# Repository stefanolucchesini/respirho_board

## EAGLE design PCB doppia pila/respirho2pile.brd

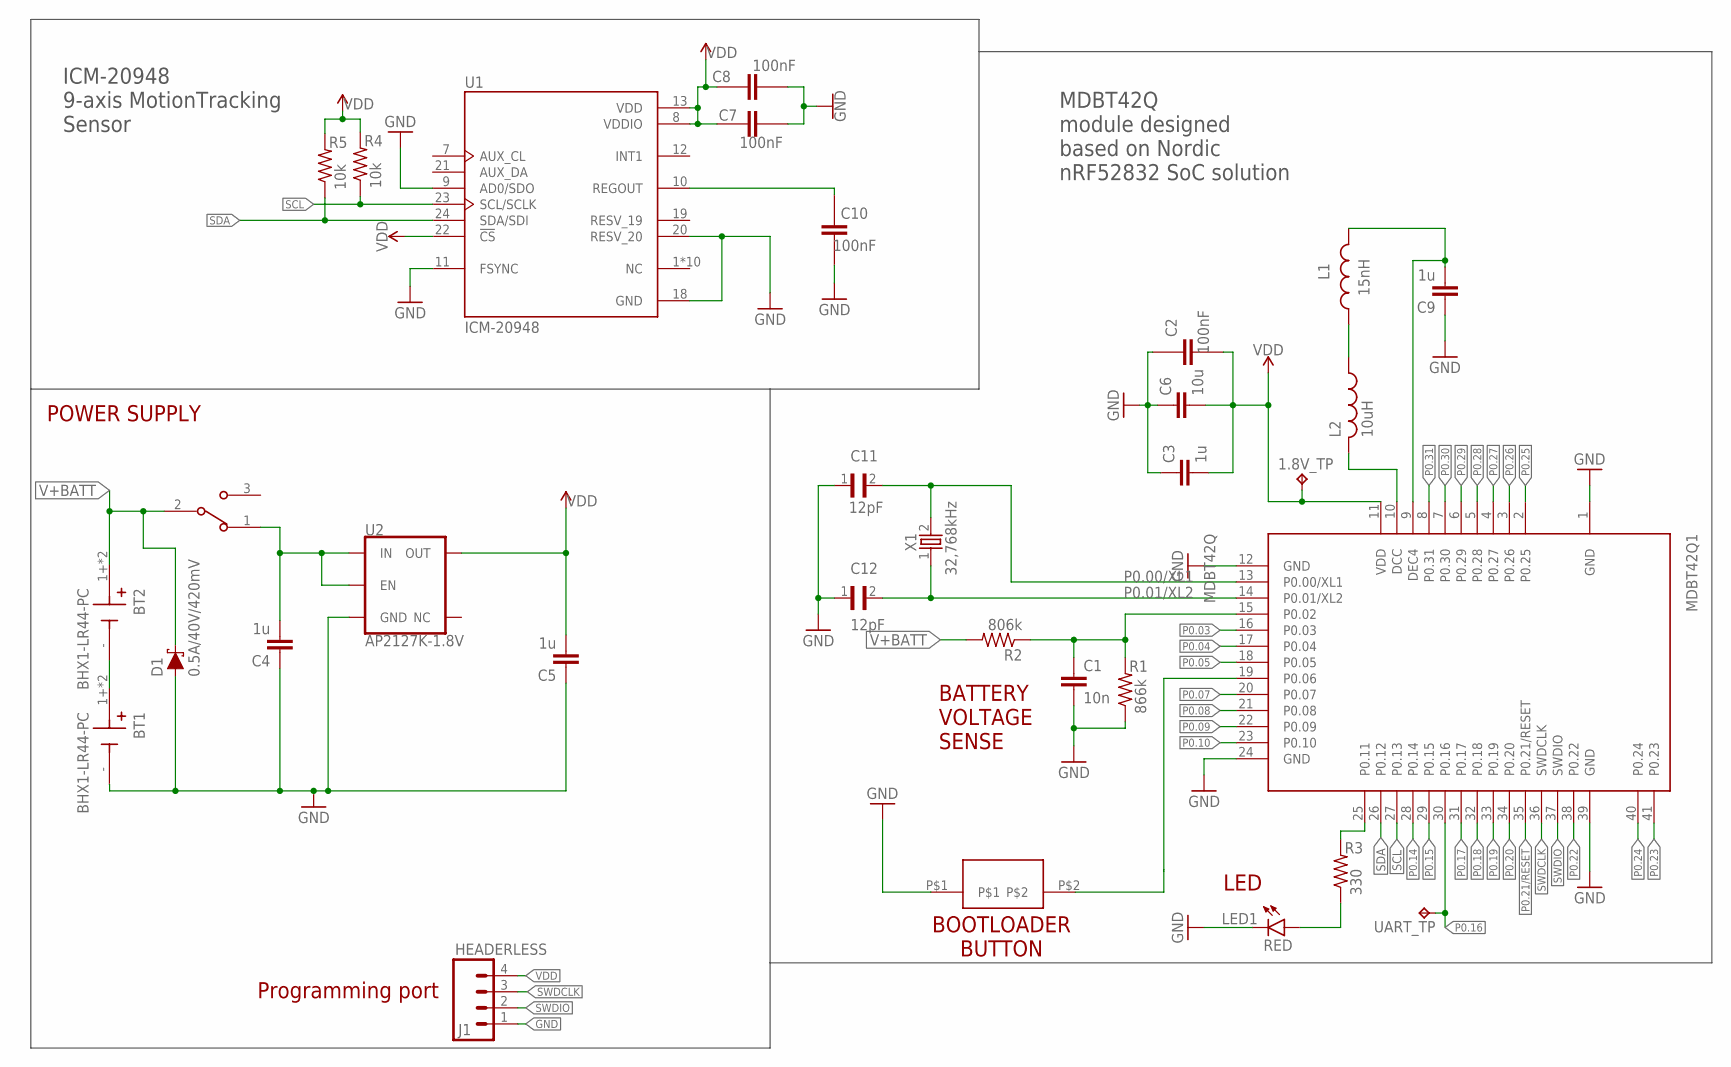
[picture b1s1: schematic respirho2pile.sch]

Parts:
1.8V_TP: TPB1,27; B1,27
BT1, BT2: BHX1-LR44-PC; BAT_BHX1-LR44-PC
C1: 10n; C0603
C2, C7, C8, C10: 100nF; CAPC1005X60
C3, C4, C5, C9: 1u; C0603
C6: 10u; C2012
C11, C12: 12pF; CAPC1005X56N
D1: 0.5A/40V/420mV; SOD-323
J1: HEADERLESS; 1X04
L1: 15nH; INDC1005X55N
L2: 10uH; RESC0603_L
LED1: RED; CHIPLED_1206
MDBT42Q1: MDBT42Q
R1: 866k; R0402
R2: 806k; R0402
R3: 330; R0402
R4, R5: 10k; R0402
SW1: EG1213; SW_EG1213
SW2: KSS231GLFS
U1: ICM-20948; QFN40P300X300X105-24N
U2: AP2127K-1.8V; SOT23-5
UART_TP: TPB1,27; B1,27
X1: 32,768kHz; XTAL_3215_N

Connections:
GND: BT1.-, C1.2, C2.2, C3.1, C4.1, C5.1, C6.1, C7.1, C8.1, C9.1, C10.1, C11.1, C12.1, D1.A, J1.1, LED1.C, MDBT42Q1.1 (GND), MDBT42Q1.12 (GND), MDBT42Q1.24 (GND), MDBT42Q1.39 (GND), R1.1, SW2.P$1, U1.9 (AD0/SDO), U1.11 (FSYNC), U1.18 (GND), U1.20 (RESV_20), U2.2 (GND)
unnamed: LED1.A, R3.1
unnamed: L2.2, MDBT42Q1.10 (DCC)
unnamed: L1.1, L2.1
unnamed: C9.2, L1.2, MDBT42Q1.9 (DEC4)
unnamed: MDBT42Q1.25 (P0.11), R3.2
unnamed: BT1.1+ (+), BT1.2+ (+), BT2.-
unnamed: C10.2, U1.10 (REGOUT)
unnamed: C4.2, SW1.1, U2.1 (IN), U2.3 (EN)
unnamed: C1.1, MDBT42Q1.15 (P0.02), R1.2, R2.1
P0.00/XL1: C11.2, MDBT42Q1.13 (P0.00/XL1), X1.2
P0.01/XL2: C12.2, MDBT42Q1.14 (P0.01/XL2), X1.1
P0.03: MDBT42Q1.16 (P0.03)
P0.04: MDBT42Q1.17 (P0.04)
P0.05: MDBT42Q1.18 (P0.05)
P0.07: MDBT42Q1.20 (P0.07)
P0.08: MDBT42Q1.21 (P0.08)
P0.09: MDBT42Q1.22 (P0.09)
P0.10: MDBT42Q1.23 (P0.10)
P0.14: MDBT42Q1.28 (P0.14)
P0.15: MDBT42Q1.29 (P0.15)
P0.16: MDBT42Q1.30 (P0.16), UART_TP.TP
P0.17: MDBT42Q1.31 (P0.17)
P0.18: MDBT42Q1.32 (P0.18)
P0.19: MDBT42Q1.33 (P0.19)
P0.20: MDBT42Q1.34 (P0.20)
P0.21/RESET: MDBT42Q1.35 (P0.21/RESET)
P0.22: MDBT42Q1.38 (P0.22)
P0.23: MDBT42Q1.41 (P0.23)
P0.24: MDBT42Q1.40 (P0.24)
P0.25: MDBT42Q1.2 (P0.25)
P0.26: MDBT42Q1.3 (P0.26)
P0.27: MDBT42Q1.4 (P0.27)
P0.28: MDBT42Q1.5 (P0.28)
P0.29: MDBT42Q1.6 (P0.29)
P0.30: MDBT42Q1.7 (P0.30)
P0.31: MDBT42Q1.8 (P0.31)
P06: MDBT42Q1.19 (P0.06), SW2.P$2
SCL: MDBT42Q1.27 (P0.13), R4.1, U1.23 (SCL/SCLK)
SDA: MDBT42Q1.26 (P0.12), R5.1, U1.24 (SDA/SDI)
SWDCLK: J1.3, MDBT42Q1.36 (SWDCLK)
SWDIO: J1.2, MDBT42Q1.37 (SWDIO)
V+BATT: BT2.1+ (+), BT2.2+ (+), D1.C, R2.2, SW1.2
VDD: 1.8V_TP.TP, C2.1, C3.2, C5.2, C6.2, C7.2, C8.2, J1.4, MDBT42Q1.11 (VDD), R4.2, R5.2, U1.8 (VDDIO), U1.13 (VDD), U1.22 (!CS), U2.5 (OUT)

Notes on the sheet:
ICM-20948 9-axis MotionTracking Sensor
MDBT42Q module designed based on Nordic nRF52832 SoC solution
LED
Programming port
POWER SUPPLY
BATTERY VOLTAGE SENSE
BOOTLOADER BUTTON

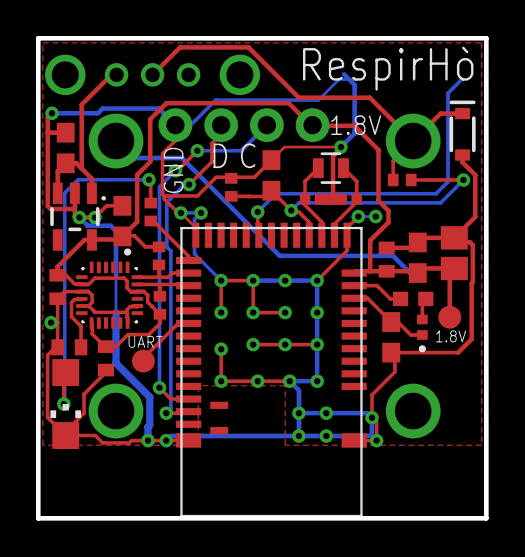
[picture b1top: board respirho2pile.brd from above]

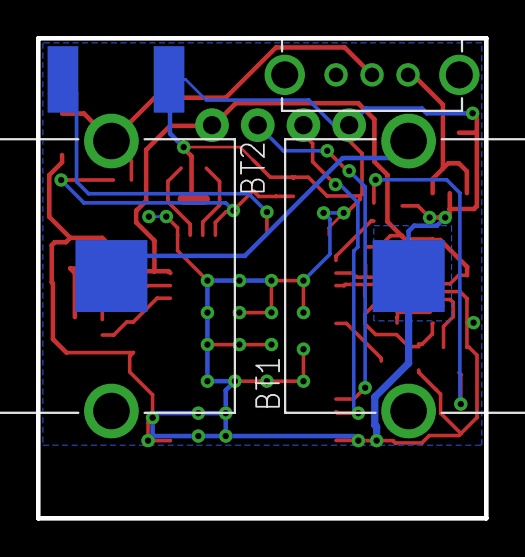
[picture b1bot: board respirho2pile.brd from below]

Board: 2 copper layers, 24.9 x 26.7 mm, 32 parts (4 on the bottom side), 20 nets.

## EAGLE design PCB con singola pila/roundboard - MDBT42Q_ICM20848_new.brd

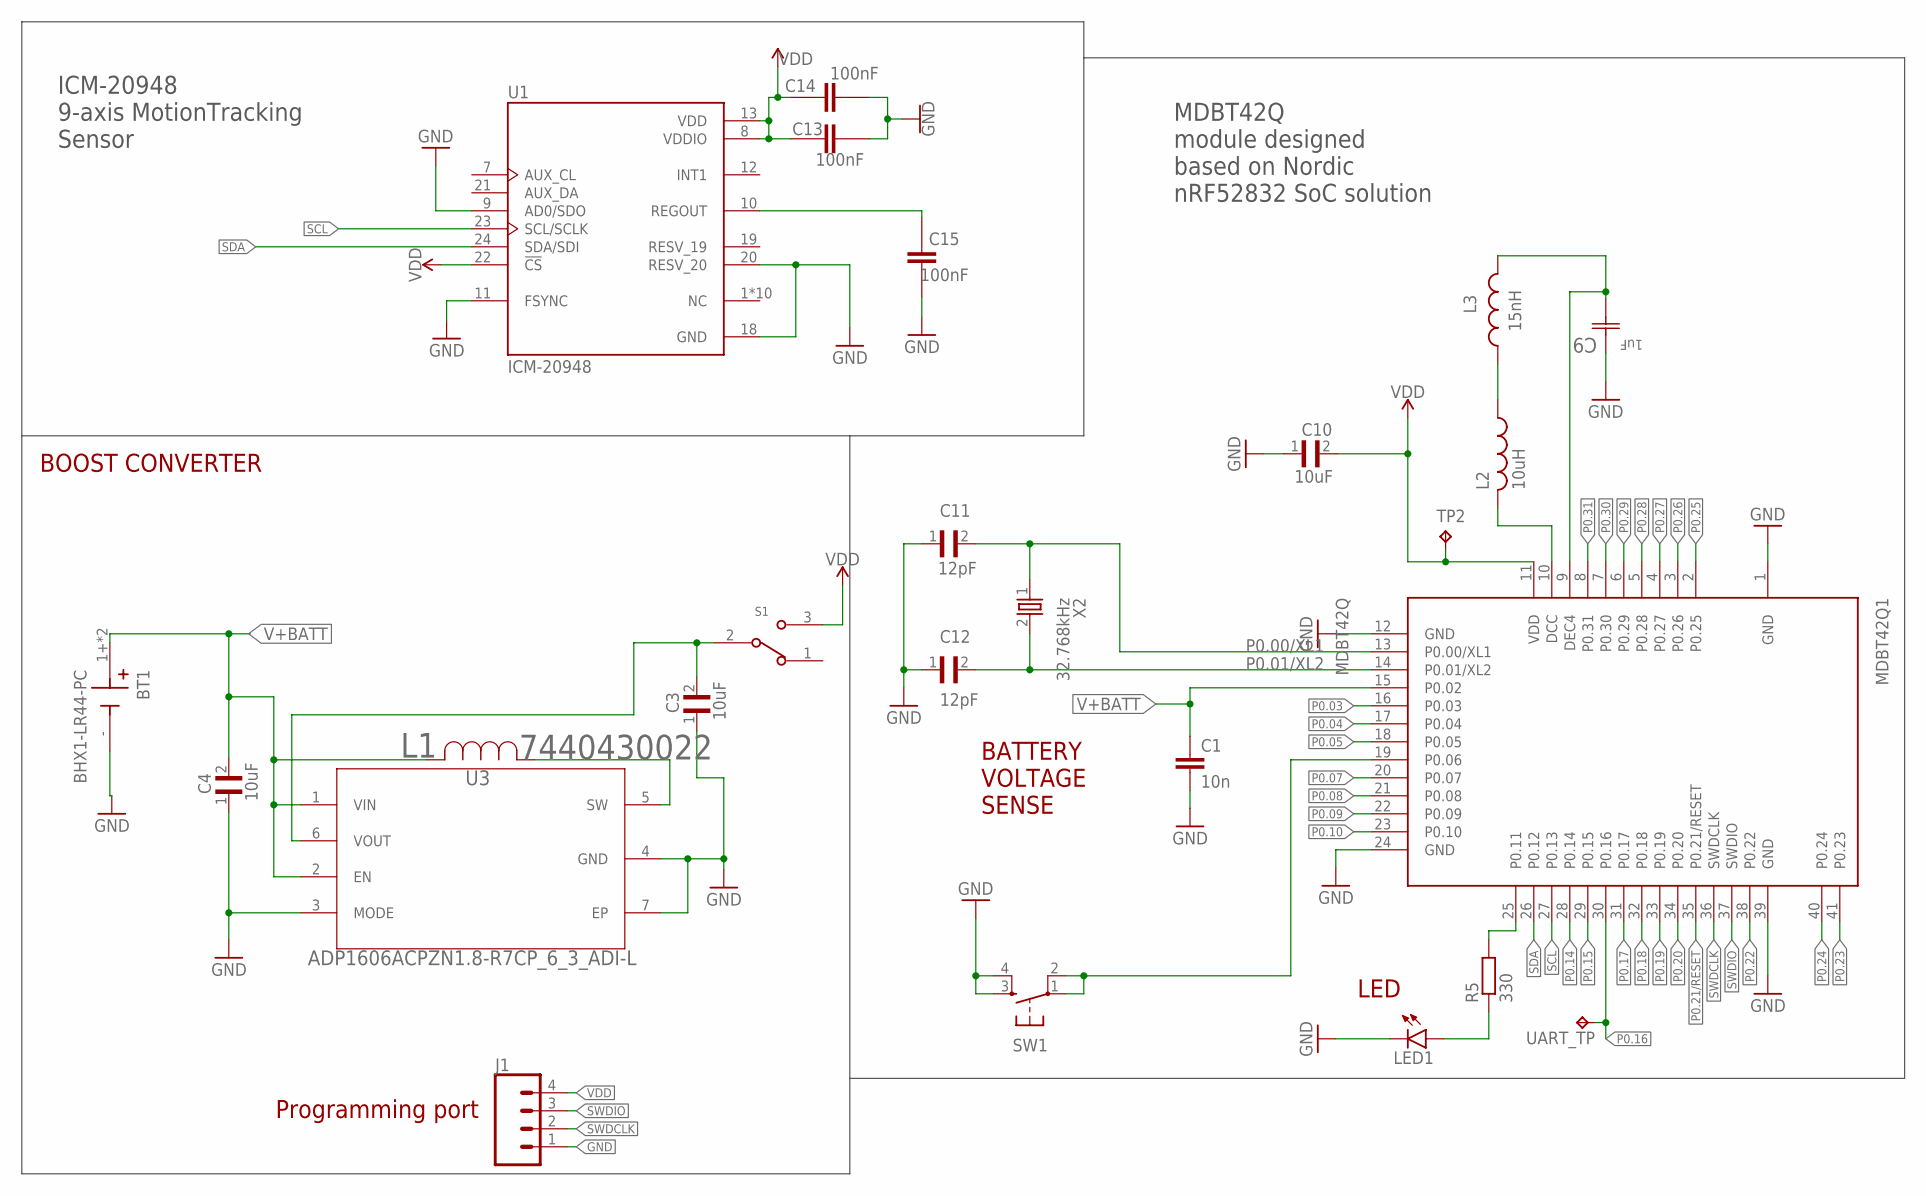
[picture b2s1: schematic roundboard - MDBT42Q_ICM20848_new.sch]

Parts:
BT1: BHX1-LR44-PC; BAT_BHX1-LR44-PC
C1: 10n; C0603
C3, C4, C10: 10uF; CAPC1608X95N
C9: 1uF; CAPC1608X90N
C11, C12: 12pF; CAPC1005X56N
C13, C14, C15: 100nF; CAPC1005X60
J1: CONN_04PTH; 1X04
L1: 7440430022; IND_7440430022_WRE
L2: 10uH; RESC0603_L
L3: 15nH; INDC1005X55N
LED1: LEDCHIPLED_1206; CHIPLED_1206
MDBT42Q1: MDBT42Q
R5: 330; R0603
S1: JS102011SAQN; SW_JS102011SAQN
SW1: SWITCH_SPST_4_PINRECT; TACTILE_SWITCH_SMD_4.6X2.8MM
TP2: TPB1,27; B1,27
U1: ICM-20948; QFN40P300X300X105-24N
U3: ADP1606ACPZN1.8-R7CP_6_3_ADI-L; CP_6_3_ADI-L
UART_TP: TPB1,27; B1,27
X2: 32.768kHz; XTAL_3215_N

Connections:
GND: BT1.-, C1.2, C3.1, C4.1, C9.1 (C1), C10.1, C11.1, C12.1, C13.1, C14.1, C15.1, J1.1, LED1.C, MDBT42Q1.1 (GND), MDBT42Q1.12 (GND), MDBT42Q1.24 (GND), MDBT42Q1.39 (GND), SW1.3, SW1.4, U1.9 (AD0/SDO), U1.11 (FSYNC), U1.18 (GND), U1.20 (RESV_20), U3.3 (MODE), U3.4 (GND), U3.7 (EP); also elsewhere on the board
IND: L1.1, U3.5 (SW)
unnamed: LED1.A, R5.1
unnamed: L2.2, MDBT42Q1.10 (DCC)
unnamed: L2.1, L3.1
unnamed: C9.2 (C2), L3.2, MDBT42Q1.9 (DEC4)
unnamed: MDBT42Q1.25 (P0.11), R5.2
unnamed: C15.2, U1.10 (REGOUT)
P0.00/XL1: C11.2, MDBT42Q1.13 (P0.00/XL1), X2.1
P0.01/XL2: C12.2, MDBT42Q1.14 (P0.01/XL2), X2.2
P0.03: MDBT42Q1.16 (P0.03)
P0.04: MDBT42Q1.17 (P0.04)
P0.05: MDBT42Q1.18 (P0.05)
P0.07: MDBT42Q1.20 (P0.07)
P0.08: MDBT42Q1.21 (P0.08)
P0.09: MDBT42Q1.22 (P0.09)
P0.10: MDBT42Q1.23 (P0.10)
P0.14: MDBT42Q1.28 (P0.14)
P0.15: MDBT42Q1.29 (P0.15)
P0.16: MDBT42Q1.30 (P0.16), UART_TP.TP
P0.17: MDBT42Q1.31 (P0.17)
P0.18: MDBT42Q1.32 (P0.18)
P0.19: MDBT42Q1.33 (P0.19)
P0.20: MDBT42Q1.34 (P0.20)
P0.21/RESET: MDBT42Q1.35 (P0.21/RESET)
P0.22: MDBT42Q1.38 (P0.22)
P0.23: MDBT42Q1.41 (P0.23)
P0.24: MDBT42Q1.40 (P0.24)
P0.25: MDBT42Q1.2 (P0.25)
P0.26: MDBT42Q1.3 (P0.26)
P0.27: MDBT42Q1.4 (P0.27)
P0.28: MDBT42Q1.5 (P0.28)
P0.29: MDBT42Q1.6 (P0.29)
P0.30: MDBT42Q1.7 (P0.30)
P0.31: MDBT42Q1.8 (P0.31)
P06: MDBT42Q1.19 (P0.06), SW1.1, SW1.2
SCL: MDBT42Q1.27 (P0.13), U1.23 (SCL/SCLK)
SDA: MDBT42Q1.26 (P0.12), U1.24 (SDA/SDI)
SWDCLK: J1.2, MDBT42Q1.36 (SWDCLK)
SWDIO: J1.3, MDBT42Q1.37 (SWDIO)
V+BATT: BT1.1+ (+), BT1.2+ (+), C1.1, C4.2, L1.2, MDBT42Q1.15 (P0.02), U3.1 (VIN), U3.2 (EN); also elsewhere on the board
VDD: C10.2, C13.2, C14.2, J1.4, MDBT42Q1.11 (VDD), S1.3, TP2.TP, U1.8 (VDDIO), U1.13 (VDD), U1.22 (!CS); also elsewhere on the board
VOUT: C3.2, S1.2, U3.6 (VOUT)

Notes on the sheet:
ICM-20948 9-axis MotionTracking Sensor
MDBT42Q module designed based on Nordic nRF52832 SoC solution
LED
Programming port
BOOST CONVERTER
BATTERY VOLTAGE SENSE

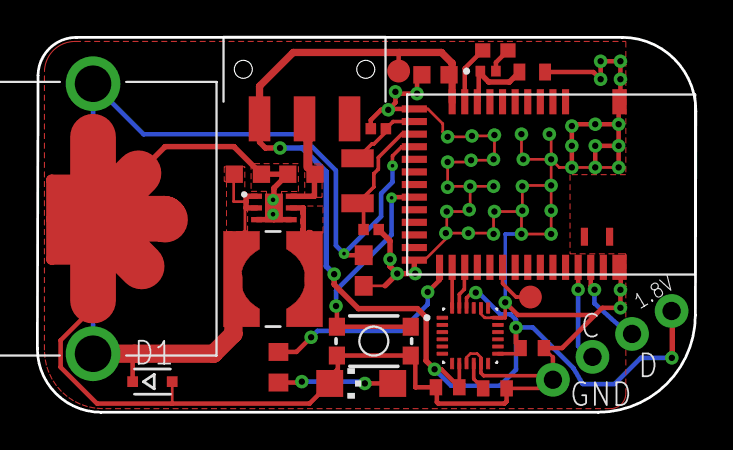
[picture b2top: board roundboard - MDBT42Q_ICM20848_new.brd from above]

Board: 2 copper layers, 36.6 x 20.8 mm, 26 parts (0 on the bottom side), 19 nets.

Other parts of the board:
1.8V_TP: TPB1,27; B1,27
D1: SOD323-R

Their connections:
GND: D1.A; also elsewhere on the board
V+BATT: D1.C; also elsewhere on the board
VDD: 1.8V_TP.TP; also elsewhere on the board

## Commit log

2021-04-05 Led più grande (1206)
    Tolti anche vari componenti inutili come le resistenze di pull up per i2c (già integrate nell'nrf) e la resistenza su INT dell'ICM
2021-04-09 Aggiunte versioni con 2 pile
2021-04-13 Routing completo versione con 2 pile
2021-04-15 Aggiunta bom(da completare)
2021-04-19 Cambiate delle footprint (R1,R2,R3) e altri piccoli miglioramenti
2021-04-19 Cambiate altre footprint e componenti non disponibili
2021-04-20 Aggiunte immagini 3d
2021-04-20 aggiunte resistenze di pull up i2c
2021-05-06 aggiunti file gerber
2021-06-28 tolte immagini contenitore vecchio

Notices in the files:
parts and their libraries:
SparkFun-Electromechanical: Licensing: Creative Commons ShareAlike 4.0 International - https://creativecommons.org/licenses/by-sa/4.0
COPYRIGHT: Copyright (C) 2018 Accelerated Designs. All rights reserved
